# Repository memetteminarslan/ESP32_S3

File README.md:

# ESP32_S3

I wanted to design such a devkit as it is highly needed in my projects.

Schematic

Pcb

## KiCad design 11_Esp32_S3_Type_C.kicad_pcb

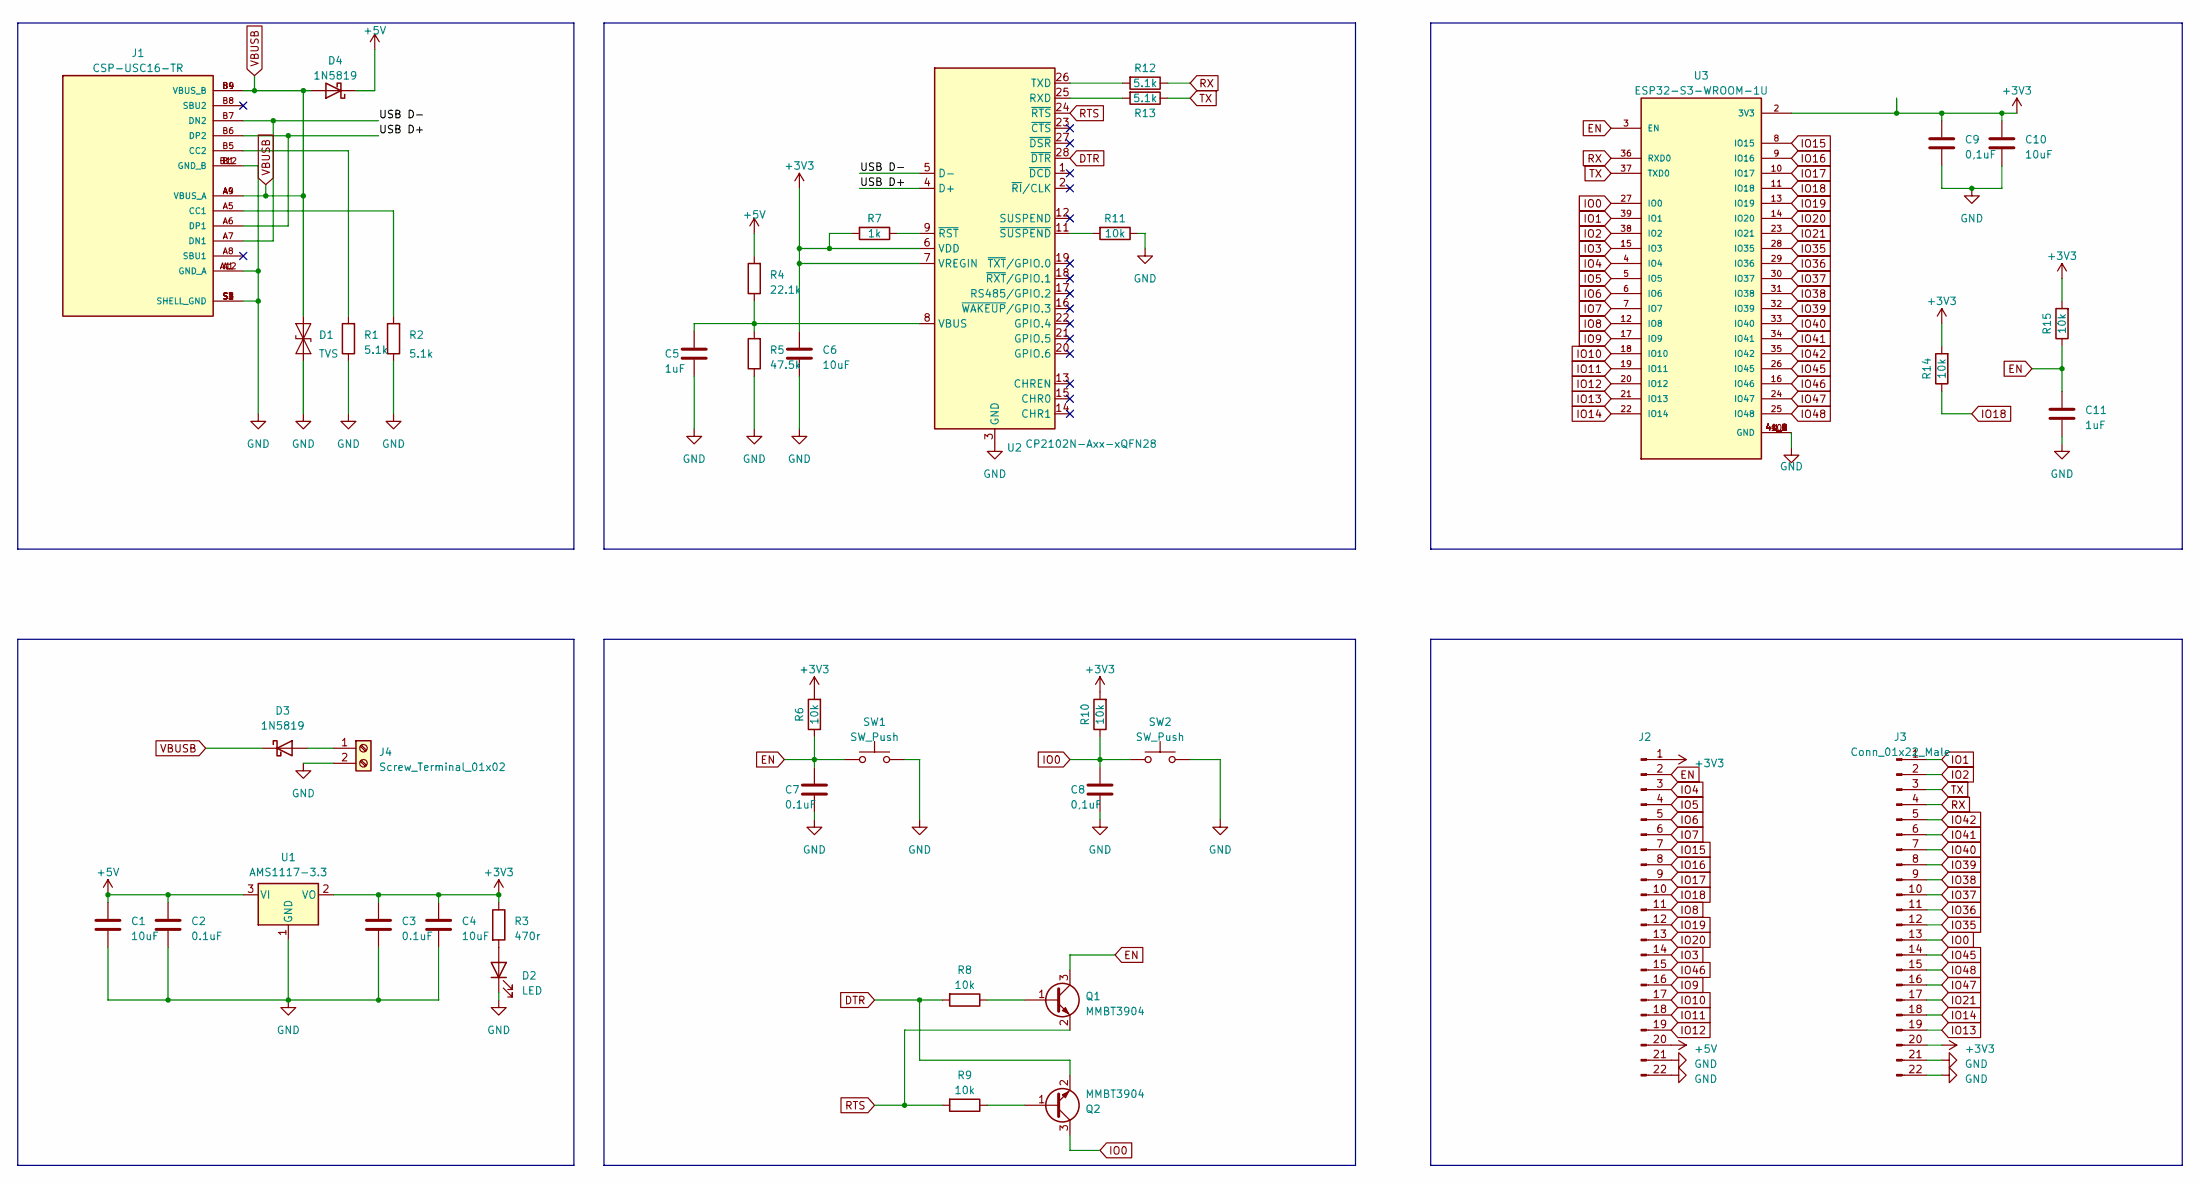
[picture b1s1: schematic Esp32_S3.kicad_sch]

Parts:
C1, C4, C6, C10: 10uF; C_0603_1608Metric
C2, C3, C7: 0.1uF; C_0603_1608Metric
C5, C11: 1uF; C_0603_1608Metric
C8, C9: 0,1uF; C_0603_1608Metric
D1: TVS; D_SOD-323_HandSoldering
D2: LED; LED_0603_1608Metric
D3, D4: 1N5819; D_SOD-123
J1: CSP-USC16-TR; VALCON_CSP-USC16-TR; PARTREV A0
J2, J3: Conn_01x22_Male; PinSocket_1x22_P2.54mm_Vertical
J4: Screw_Terminal_01x02; PinHeader_1x02_P2.54mm_Vertical
Q1, Q2: MMBT3904; SOT-23
R1, R2: 5.1k; R_0402_1005Metric
R3: 470r; R_0603_1608Metric
R4: 22.1k; R_0603_1608Metric
R5: 47.5k; R_0603_1608Metric
R6, R8, R9, R10, R11, R14, R15: 10k; R_0603_1608Metric
R7: 1k; R_0603_1608Metric
R12, R13: 5.1k; R_0603_1608Metric
SW1, SW2: SW_Push; SW_TL1015AF160QG
U1: AMS1117-3.3; SOT-223-3_TabPin2
U2: CP2102N-Axx-xQFN28; QFN-28-1EP_5x5mm_P0.5mm_EP3.35x3.35mm
U3: ESP32-S3-WROOM-1U; ESP32-S3-WROOM-1; PARTREV v0.6

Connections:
+3V3: C3.1, C4.1, C6.1, C9.1, C10.1, J2.1, J3.20, R3.1, R6.2, R7.2, R10.2, R14.2, R15.2, U1.2 (VO), U2.6 (VDD), U2.7 (VREGIN), U3.2 (3V3)
+5V: C1.1, C2.1, D4.1 (K), J2.20, R4.2, U1.3 (VI)
/USB D+: J1.A6 (DP1), J1.B6 (DP2), U2.4 (D+)
/USB D-: J1.A7 (DN1), J1.B7 (DN2), U2.5 (D-)
DTR: Q2.2 (E), R8.2, U2.28 (~DTR)
EN: C7.1, C11.1, J2.2, Q1.3 (C), R6.1, R15.1, SW1.1, U3.3 (EN)
GND: C1.2, C2.2, C3.2, C4.2, C5.2, C6.2, C7.2, C8.2, C9.2, C10.2, C11.2, D1.1 (A1), D2.1 (K), J1.A1 (GND_A), J1.A12 (GND_A), J1.B1 (GND_B), J1.B12 (GND_B), J1.S1 (SHELL_GND), J1.S2 (SHELL_GND), J1.S3 (SHELL_GND), J1.S4 (SHELL_GND), J2.21, J2.22, J3.21, J3.22, J4.2, R1.1, R2.1, R5.1, R11.1, SW1.2, SW2.2, U1.1 (GND), U2.3 (GND), U2.29 (GND), U3.1 (GND), U3.40 (GND), U3.41_1 (GND), U3.41_2 (GND), U3.41_3 (GND), U3.41_4 (GND), U3.41_5 (GND), U3.41_6 (GND), U3.41_7 (GND), U3.41_8 (GND), U3.41_9 (GND)
IO0: C8.1, J3.13, Q2.3 (C), R10.1, SW2.1, U3.27 (IO0)
IO1: J3.1, U3.39 (IO1)
IO2: J3.2, U3.38 (IO2)
IO3: J2.14, U3.15 (IO3)
IO4: J2.3, U3.4 (IO4)
IO5: J2.4, U3.5 (IO5)
IO6: J2.5, U3.6 (IO6)
IO7: J2.6, U3.7 (IO7)
IO8: J2.11, U3.12 (IO8)
IO9: J2.16, U3.17 (IO9)
IO10: J2.17, U3.18 (IO10)
IO11: J2.18, U3.19 (IO11)
IO12: J2.19, U3.20 (IO12)
IO13: J3.19, U3.21 (IO13)
IO14: J3.18, U3.22 (IO14)
IO15: J2.7, U3.8 (IO15)
IO16: J2.8, U3.9 (IO16)
IO17: J2.9, U3.10 (IO17)
IO18: J2.10, R14.1, U3.11 (IO18)
IO19: J2.12, U3.13 (IO19)
IO20: J2.13, U3.14 (IO20)
IO21: J3.17, U3.23 (IO21)
IO35: J3.12, U3.28 (IO35)
IO36: J3.11, U3.29 (IO36)
IO37: J3.10, U3.30 (IO37)
IO38: J3.9, U3.31 (IO38)
IO39: J3.8, U3.32 (IO39)
IO40: J3.7, U3.33 (IO40)
IO41: J3.6, U3.34 (IO41)
IO42: J3.5, U3.35 (IO42)
IO45: J3.14, U3.26 (IO45)
IO46: J2.15, U3.16 (IO46)
IO47: J3.16, U3.24 (IO47)
IO48: J3.15, U3.25 (IO48)
unnamed: D2.2 (A), R3.2
unnamed: D3.2 (A), J4.1
unnamed: J1.A5 (CC1), R2.2
unnamed: J1.B5 (CC2), R1.2
unnamed: Q1.1 (B), R8.1
unnamed: Q2.1 (B), R9.1
unnamed: R13.2, U2.25 (RXD)
unnamed: R12.2, U2.26 (TXD)
unnamed: C5.1, R4.1, R5.2, U2.8 (VBUS)
unnamed: R7.1, U2.9 (~RST)
unnamed: R11.2, U2.11 (~SUSPEND)
RTS: Q1.2 (E), R9.2, U2.24 (~RTS)
RX: J3.4, R12.1, U3.36 (RXD0)
TX: J3.3, R13.1, U3.37 (TXD0)
VBUSB: D1.2 (A2), D3.1 (K), D4.2 (A), J1.A4 (VBUS_A), J1.A9 (VBUS_A), J1.B4 (VBUS_B), J1.B9 (VBUS_B)

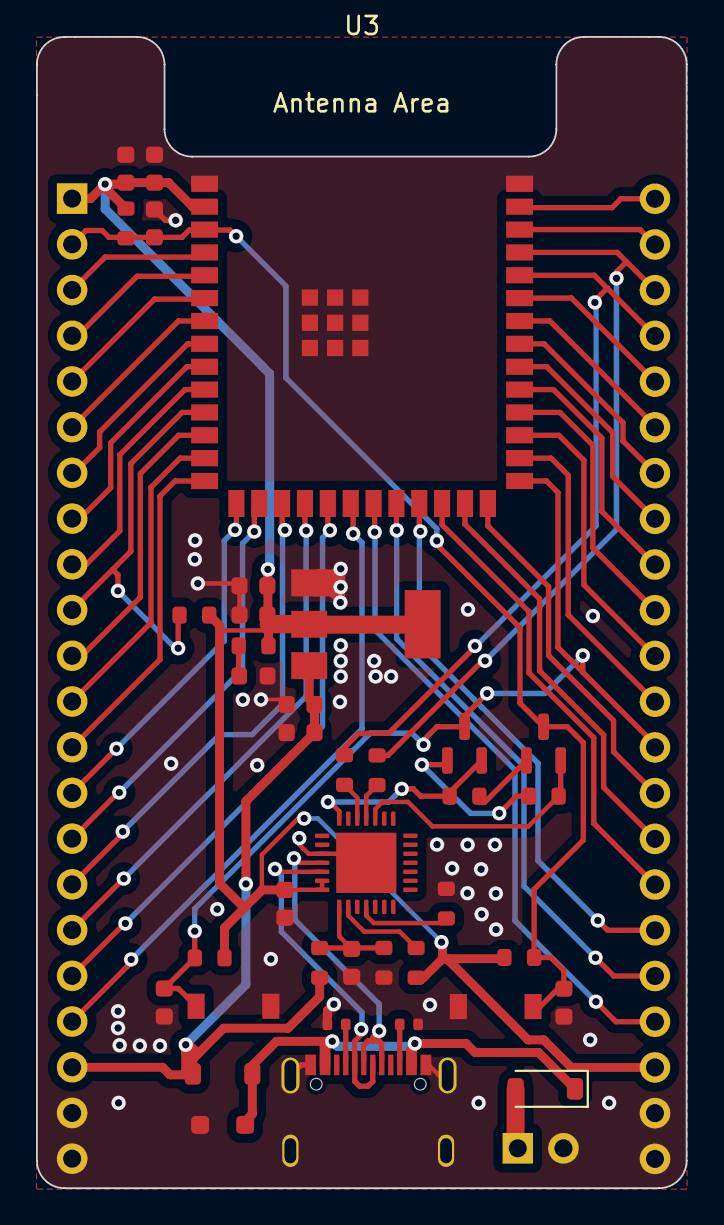
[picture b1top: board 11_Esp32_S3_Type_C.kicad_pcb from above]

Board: 2 copper layers, 36.1 x 64.0 mm, 41 parts (0 on the bottom side), 56 nets.
